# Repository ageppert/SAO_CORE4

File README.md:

# SAO_CORE4

A Nibble of Core Memory

Follow this project at: https://hackaday.io/project/197235-sao-core4-a-nibble-of-core-memory-with-i2c

Hardware Version 0.2.0 - Work in progres - reducing board size - add button - simplify.

Hardware Version 0.1.1 hand reworked prototype, simplified and re-routed row drive transistor signals to simplify firmware development. This is the version that is currently the functional prototype. These changes will be in 0.2.0.

Hardware Version 0.1 as prototyped

Hardware Version 0.1 render

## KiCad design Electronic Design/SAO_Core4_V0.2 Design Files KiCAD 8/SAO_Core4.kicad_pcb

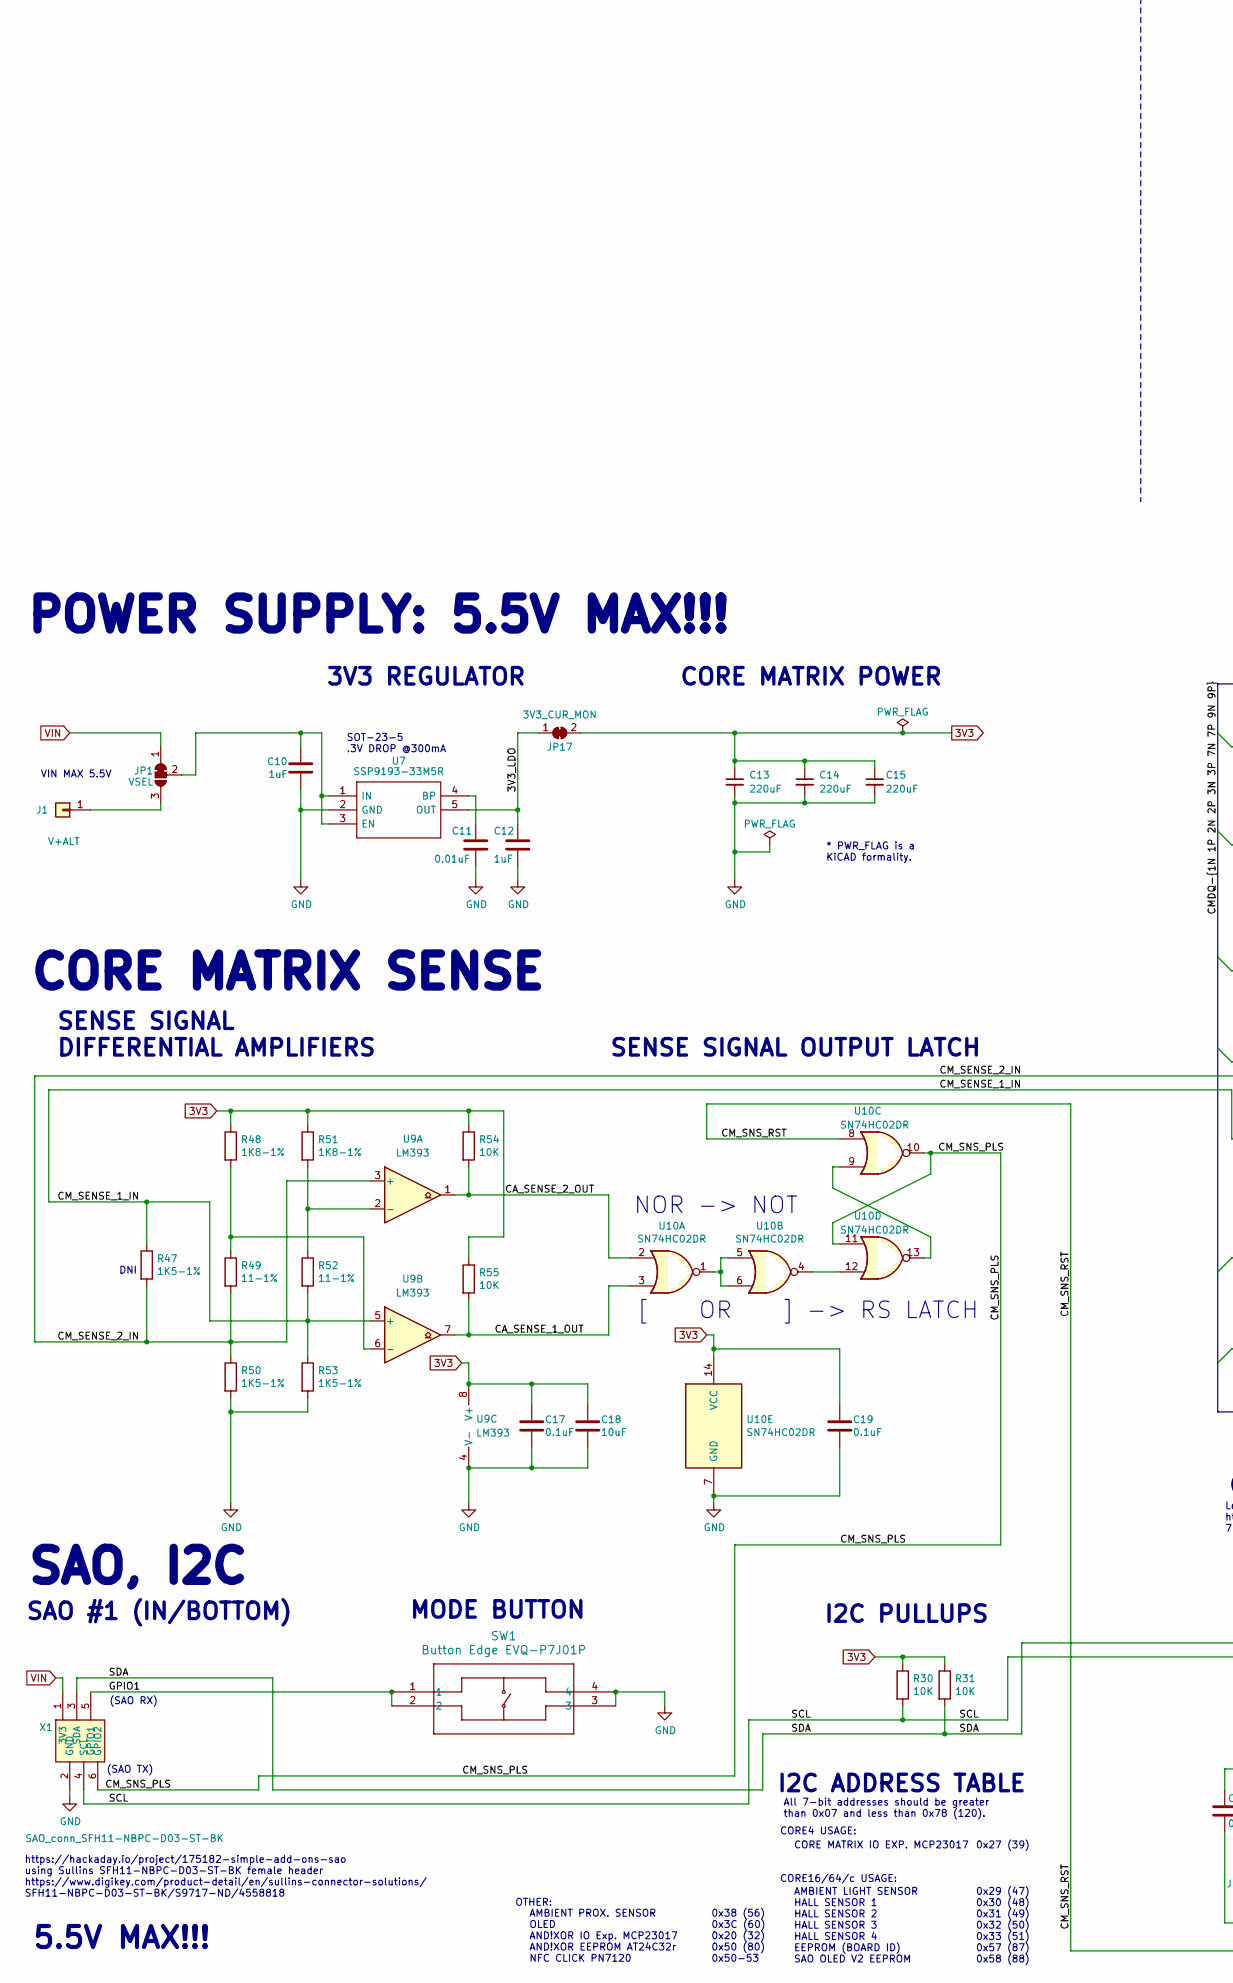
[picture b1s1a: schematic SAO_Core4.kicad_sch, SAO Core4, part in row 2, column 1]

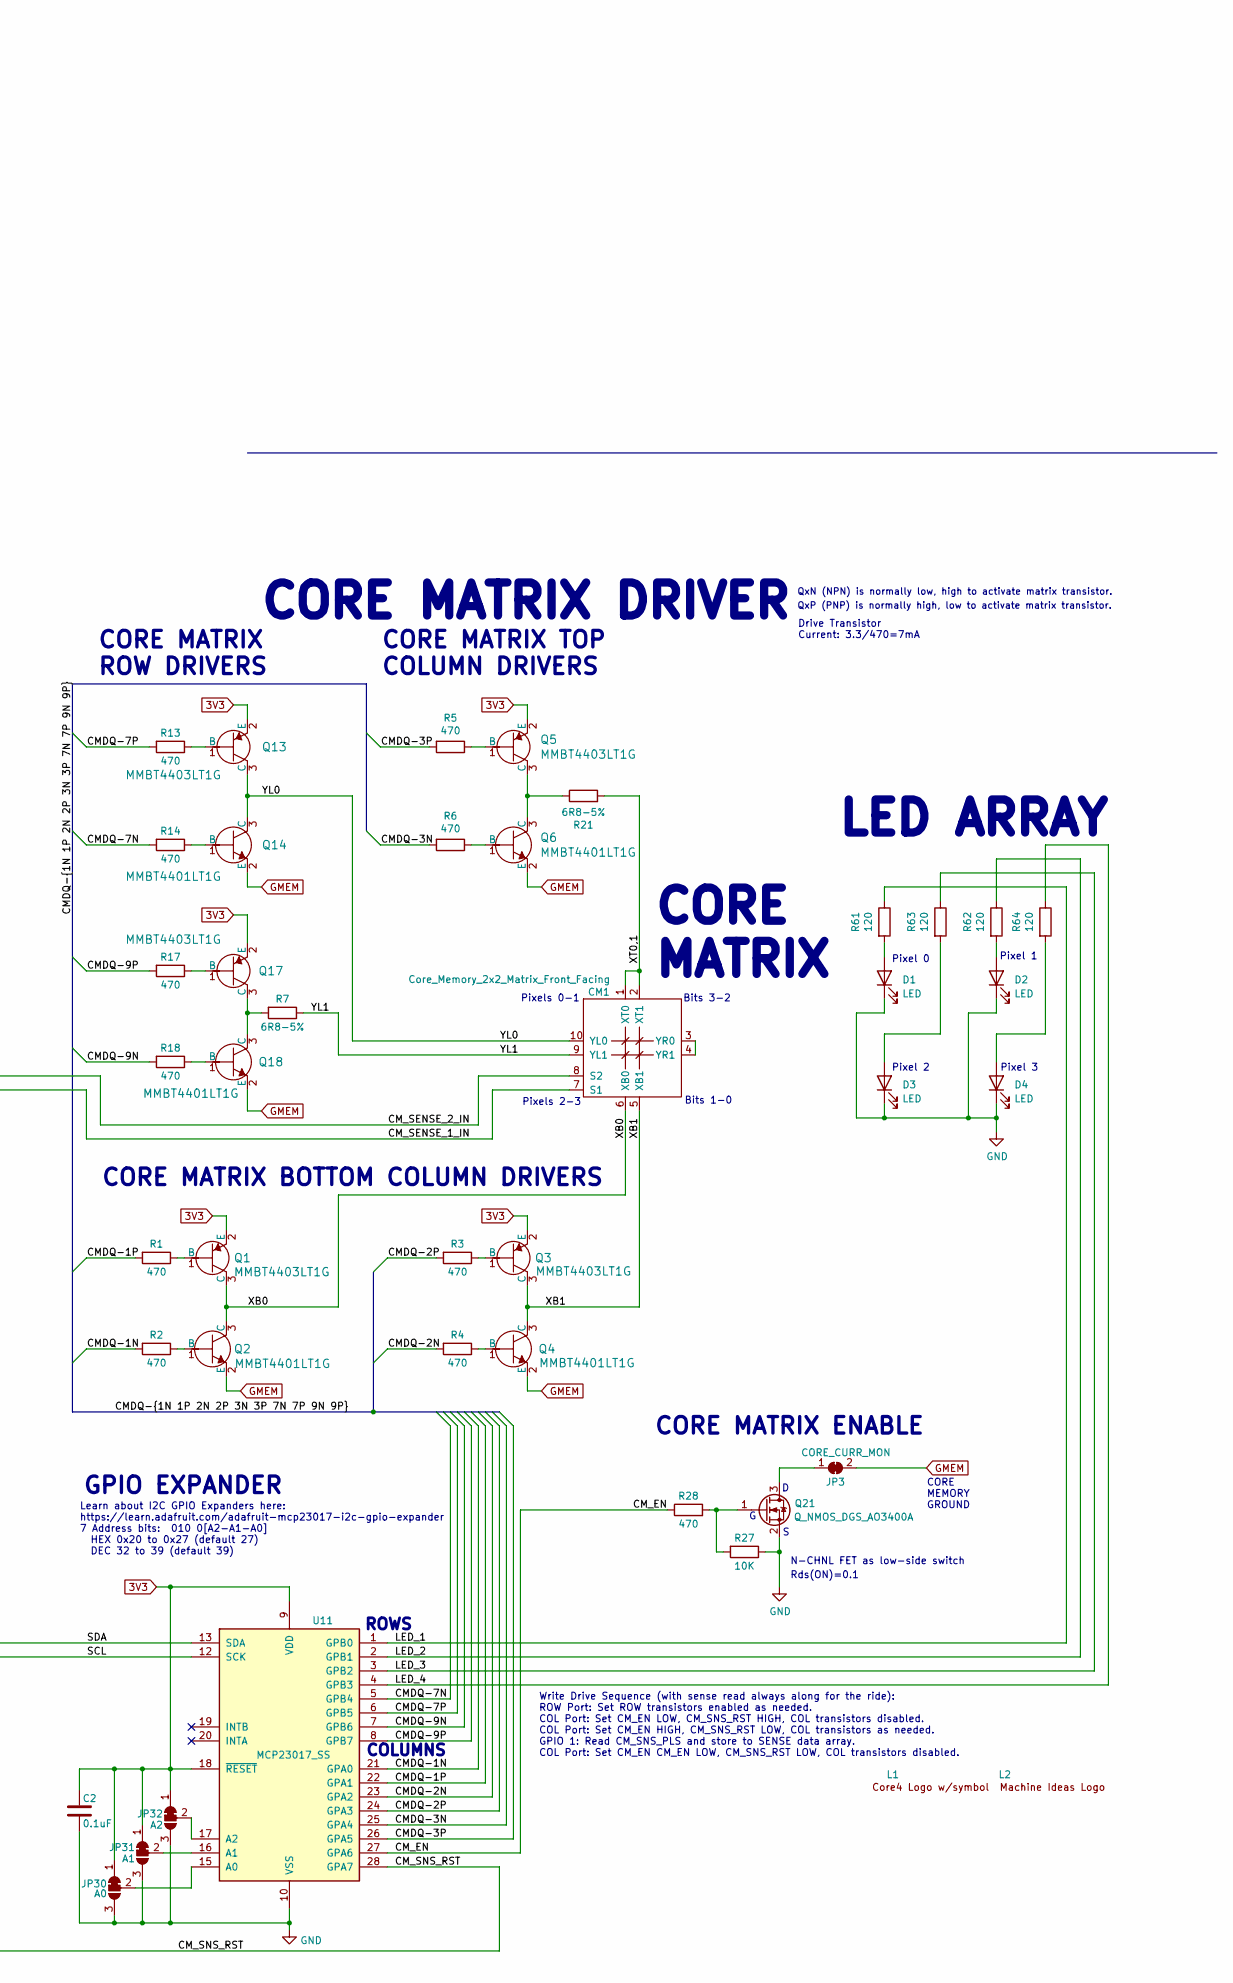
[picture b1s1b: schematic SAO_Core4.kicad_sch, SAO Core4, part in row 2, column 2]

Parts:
C2, C17, C19: 0.1uF; C_0805_2012Metric; LCSC C28233
C10, C12: 1uF; C_0805_2012Metric; LCSC C28323
C11: 0.01uF; C_0805_2012Metric; LCSC C1710
C13, C14, C15: 220uF; C_1206_3216Metric; LCSC C412252
C18: 10uF; C_0805_2012Metric; LCSC C17024
CM1: Core_Memory_2x2_Matrix_Front_Facing; core_4_6.75mm_square_front_facing
D1, D2, D3, D4: LED; LED_1206_3216Metric_RevMnt_Hole1.8x2.4mm_custom; Manufacturer_Part_Number XL-3216UOC-FB; LCSC C3646936
J1: V+ALT; PinSocket_1x01_P1.27mm_Vertical
JP1: VSEL; SolderJumper-3_P1.3mm_Bridged12_Pad1.0x1.5mm
JP3: CORE_CURR_MON; SolderJumper-2_P1.3mm_Bridged_RoundedPad1.0x1.5mm
JP17: 3V3_CUR_MON; SolderJumper-2_P1.3mm_Bridged_RoundedPad1.0x1.5mm
JP30: A0; SolderJumper-3_P1.3mm_Bridged12_Pad1.0x1.5mm
JP31: A1; SolderJumper-3_P1.3mm_Bridged12_Pad1.0x1.5mm
JP32: A2; SolderJumper-3_P1.3mm_Bridged12_Pad1.0x1.5mm
L1: Core4_w_core_symbol
L2: Machine_Ideas_logo
Q1, Q3, Q5, Q13, Q17: MMBT4403LT1G; SOT-23-3; MPN MMBT4403LT1G; Digi-Key_PN MMBT4403LT1GOSCT-ND
Q2, Q4, Q6, Q14, Q18: MMBT4401LT1G; SOT-23-3; MPN MMBT4401LT1G; Digi-Key_PN MMBT4401LT1GOSCT-ND
Q21: Q_NMOS_DGS_AO3400A; SOT-23-3; LCSC C20917
R1, R2, R3, R4, R5, R6, R13, R14, R17, R18, R28: 470; R_0805_2012Metric; LCSC C17710
R7, R21: 6R8-5%; R_0805_2012Metric; LCSC C17774
R27, R30, R31, R54, R55: 10K; R_0805_2012Metric; LCSC C17414
R47, R50, R53: 1K5-1%; R_0805_2012Metric; LCSC C4310
R48, R51: 1K8-1%; R_0805_2012Metric; LCSC C17398
R49, R52: 11-1%; R_0805_2012Metric; LCSC C17430
R61, R62, R63, R64: 120; R_0805_2012Metric; LCSC C17437
SW1: Button Edge EVQ-P7J01P; SMD4_SW_EVQP7J_PAN; LCSC C2828254
U7: SSP9193-33M5R; SOT-23-5; Manufacturer_Part_Number SGM2007-3.3XN5/TR; Mouser Part Number SGM2007-3.3XN5/TR
U9: LM393; SOIC-8_W3.9mm; LCSC C7955
U10: SN74HC02DR; SOIC-14_3.9x8.7mm_P1.27mm; MPN SN74HC02DR; LCSC C6809
U11: MCP23017_SS; SSOP-28_5.3x10.2mm_P0.65mm; LCSC C506653
X1: SAO_conn_SFH11-NBPC-D03-ST-BK; Badgelife-SAOv169-BADGE-2x3-Edge-Connect-no-front-text; MPN SFH11-NBPC-D03-ST-BK

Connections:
3V3: C2.1, C13.1, C14.1, C15.1, C17.1, C18.1, C19.1, JP17.2 (B), JP30.1 (A), JP31.1 (A), JP32.1 (A), Q1.2 (E), Q3.2 (E), Q5.2 (E), Q13.2 (E), Q17.2 (E), R30.1, R31.1, R48.1, R51.1, R54.1, R55.1, U9.8 (V+), U10.14 (VCC), U11.9 (VDD), U11.18 (~RESET)
/3V3_LDO: C12.1, JP17.1 (A), U7.5 (OUT)
/CA_SENSE_1_OUT: R55.2, U9.7, U10.3
/CA_SENSE_2_OUT: R54.2, U9.1, U10.2
/CMDQ-1N: R2.2, U11.21 (GPA0)
/CMDQ-1P: R1.2, U11.22 (GPA1)
/CMDQ-2N: R4.2, U11.23 (GPA2)
/CMDQ-2P: R3.2, U11.24 (GPA3)
/CMDQ-3N: R6.2, U11.25 (GPA4)
/CMDQ-3P: R5.2, U11.26 (GPA5)
/CMDQ-7N: R14.2, U11.5 (GPB4)
/CMDQ-7P: R13.2, U11.6 (GPB5)
/CMDQ-9N: R18.2, U11.7 (GPB6)
/CMDQ-9P: R17.2, U11.8 (GPB7)
/CM_EN: R28.1, U11.27 (GPA6)
/CM_SENSE_1_IN: CM1.7 (S1), R47.1, R52.2, R53.1, U9.5 (+)
/CM_SENSE_2_IN: CM1.8 (S2), R47.2, R49.2, R50.1, U9.3 (+)
/CM_SNS_PLS: U10.10, U10.11, X1.6 (GPIO2)
/CM_SNS_RST: U10.8, U11.28 (GPA7)
/GPIO1: SW1.1, SW1.2, X1.5 (GPIO1)
/LED_1: R61.1, U11.1 (GPB0)
/LED_2: R62.1, U11.2 (GPB1)
/LED_3: R63.1, U11.3 (GPB2)
/LED_4: R64.1, U11.4 (GPB3)
/SCL: R30.2, U11.12 (SCK), X1.4 (SCL)
/SDA: R31.2, U11.13 (SDA), X1.3 (SDA)
/XB0: CM1.6 (XB0), Q1.3 (C), Q2.3 (C)
/XB1: CM1.5 (XB1), Q3.3 (C), Q4.3 (C)
/XT0,1: CM1.1 (XT0), CM1.2 (XT1), R21.2
/YL0: CM1.10 (YL0), Q13.3 (C), Q14.3 (C)
/YL1: CM1.9 (YL1), R7.1
GMEM: JP3.2 (B), Q2.2 (E), Q4.2 (E), Q6.2 (E), Q14.2 (E), Q18.2 (E)
GND: C2.2, C10.2, C11.2, C12.2, C13.2, C14.2, C15.2, C17.2, C18.2, C19.2, D1.1 (K), D2.1 (K), D3.1 (K), D4.1 (K), JP30.3 (B), JP31.3 (B), JP32.3 (B), Q21.2 (S), R27.1, R50.2, R53.2, SW1.3, SW1.4, U7.2 (GND), U9.4 (V-), U10.7 (GND), U11.10 (VSS), X1.2 (GND)
unnamed: CM1.3 (YR0), CM1.4 (YR1)
unnamed: D1.2 (A), R61.2
unnamed: D2.2 (A), R62.2
unnamed: D3.2 (A), R63.2
unnamed: D4.2 (A), R64.2
unnamed: J1.1, JP1.3 (B)
unnamed: C10.1, JP1.2 (C), U7.1 (IN), U7.3 (EN)
unnamed: JP3.1 (A), Q21.3 (D)
unnamed: JP30.2 (C), U11.15 (A0)
unnamed: JP31.2 (C), U11.16 (A1)
unnamed: JP32.2 (C), U11.17 (A2)
unnamed: Q1.1 (B), R1.1
unnamed: Q2.1 (B), R2.1
unnamed: Q3.1 (B), R3.1
unnamed: Q4.1 (B), R4.1
unnamed: Q5.1 (B), R5.1
unnamed: Q5.3 (C), Q6.3 (C), R21.1
unnamed: Q6.1 (B), R6.1
unnamed: Q13.1 (B), R13.1
unnamed: Q14.1 (B), R14.1
unnamed: Q17.1 (B), R17.1
unnamed: Q17.3 (C), Q18.3 (C), R7.2
unnamed: Q18.1 (B), R18.1
unnamed: Q21.1 (G), R27.2, R28.2
unnamed: C11.1, U7.4 (BP)
unnamed: R51.2, R52.1, U9.2 (-)
unnamed: R48.2, R49.1, U9.6 (-)
unnamed: U10.1, U10.5, U10.6
unnamed: U10.4, U10.12
unnamed: U10.9, U10.13
VIN: JP1.1 (A), X1.1 (3V3)

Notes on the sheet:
Bits 1-0
Pixel 0
QxP (PNP) is normally high, low to activate matrix transistor.
NOR -> NOT
AMBIENT PROX. SENSOR OLED AND!XOR IO Exp. MCP23017 AND!XOR EEPROM AT24C32r NFC CLICK PN7120
https://hackaday.io/project/175182-simple-add-ons-sao using Sullins SFH11-NBPC-D03-ST-BK female header https://www.digikey.com/product-detail/en/sullins-connector-solutions/ SFH11-NBPC-D03-ST-BK/S9717-ND/4558818
Bits 3-2
CORE MEMORY GROUND
N-CHNL FET as low-side switch
SENSE SIGNAL OUTPUT LATCH
[ OR ] -> RS LATCH
CORE MATRIX ROW DRIVERS
CORE4 USAGE:
CORE MATRIX IO EXP. MCP23017
Pixels 0-1
CORE MATRIX BOTTOM COLUMN DRIVERS
SOT-23-5 .3V DROP @300mA
MODE BUTTON
0x29 (47) 0x30 (48) 0x31 (49) 0x32 (50) 0x33 (51) 0x57 (87) 0x58 (88)
QxN (NPN) is normally low, high to activate matrix transistor.
ROWS
Pixel 2
COLUMNS
* PWR_FLAG is a KiCAD formality.
Pixel 1
GPIO EXPANDER
Rds(ON)=0.1
AMBIENT LIGHT SENSOR HALL SENSOR 1 HALL SENSOR 2 HALL SENSOR 3 HALL SENSOR 4 EEPROM (BOARD ID) SAO OLED V2 EEPROM
CORE MATRIX ENABLE
POWER SUPPLY: 5.5V MAX!!!
Drive Transistor Current: 3.3/470=7mA
CORE MATRIX DRIVER
CORE MATRIX TOP COLUMN DRIVERS
5.5V MAX!!!
3V3 REGULATOR
VIN MAX 5.5V
(SAO TX)
Write Drive Sequence (with sense read always along for the ride): ROW Port: Set ROW transistors enabled as needed. COL Port: Set CM_EN LOW, CM_SNS_RST HIGH, COL transistors disabled. COL Port: Set CM_EN HIGH, CM_SNS_RST LOW, COL transistors as needed. GPIO 1: Read CM_SNS_PLS and store to SENSE data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
0x38 (56) 0x3C (60) 0x20 (32) 0x50 (80) 0x50-53
SAO #1 (IN/BOTTOM)

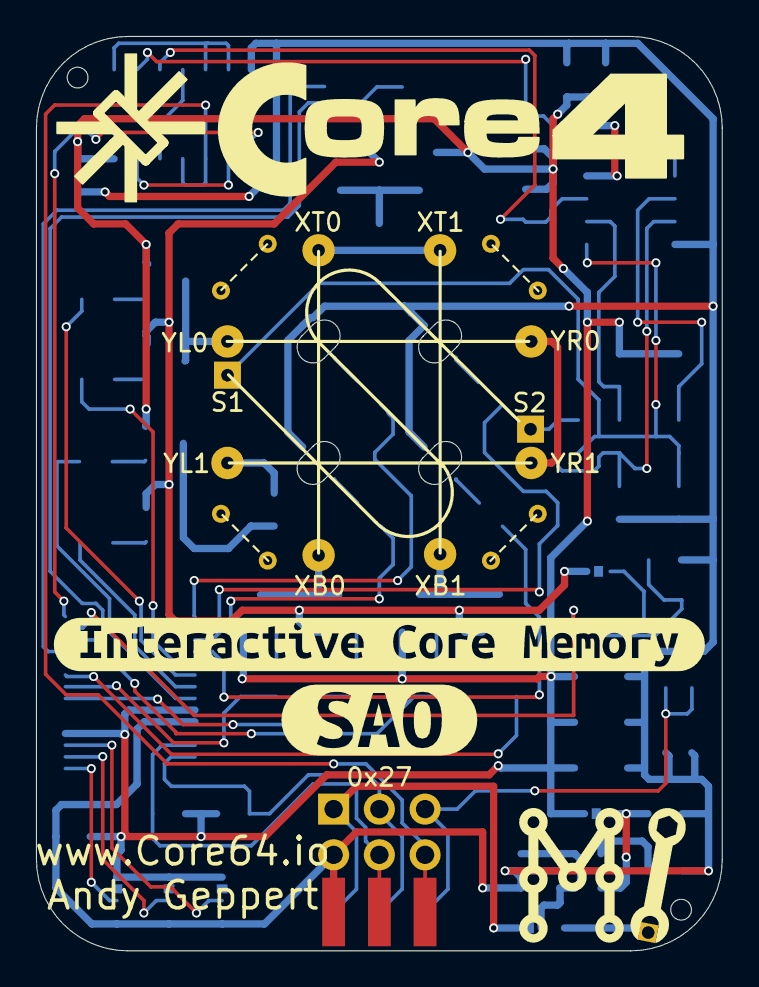
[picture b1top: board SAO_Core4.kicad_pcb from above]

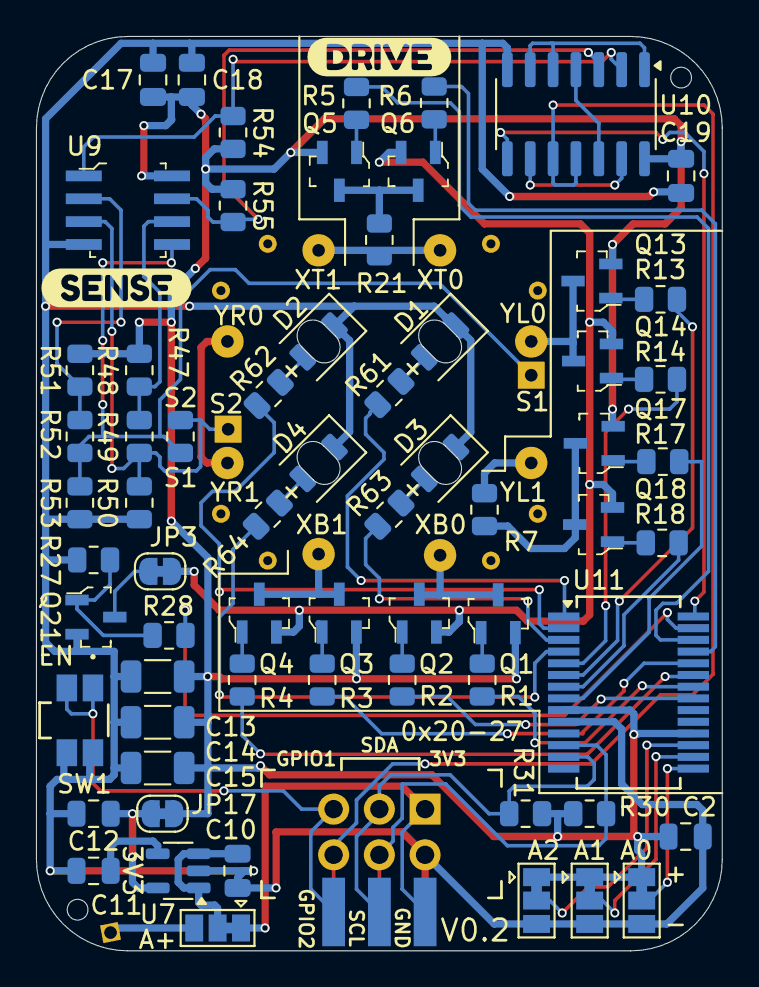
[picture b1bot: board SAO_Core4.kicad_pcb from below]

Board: 2 copper layers, 38.1 x 50.8 mm, 74 parts (68 on the bottom side), 64 nets.

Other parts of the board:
kibuzzard-66D35F07: G***; kibuzzard-66D35F07
kibuzzard-66D35F61: G***; kibuzzard-66D35F61
kibuzzard-64178DE8: G***; kibuzzard-64178DE8
kibuzzard-64178DF4: G***; kibuzzard-64178DF4

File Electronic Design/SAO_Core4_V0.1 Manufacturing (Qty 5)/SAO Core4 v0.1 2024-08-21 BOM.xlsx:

Comment | Designator | Footprint | LCSC Part Number | Substituted
0.1uF | C2, C17, C19 | Capacitor_SMD:C_0805_2012Metric | C28233
1uF | C10, C12 | Capacitor_SMD:C_0805_2012Metric | C28323
0.01uF | C11 | Capacitor_SMD:C_0805_2012Metric | C1710
220uF | C13, C14, C15 | Capacitor_SMD:C_1206_3216Metric | C412252
10uF | C18 | Capacitor_SMD:C_0805_2012Metric | C17024
LED | D1, D2, D3, D4 | Andy_Footprint_Library:LED_1206_3216Metric_RevMnt_Hole1.8x2.4mm_custom | C3646936
MMBT4403LT1G | Q1, Q3, Q5, Q13, Q17 | digikey-footprints:SOT-23-3 | C78864
MMBT4401LT1G | Q2, Q4, Q6, Q14, Q18 | digikey-footprints:SOT-23-3 | C31776
Q_NMOS_DGS_AO3400A | Q21 | digikey-footprints:SOT-23-3 | C20917
SL3401A | Q22 | digikey-footprints:SOT-23-3 | C350311
470 | R1, R2, R3, R4, R5, R6, R13, R14, R17, R18, R28 | Resistor_SMD:R_0805_2012Metric | C17710
8R2-5% | R7, R21 | Resistor_SMD:R_0805_2012Metric | C17830
4K7 | R27, R44 | Resistor_SMD:R_0805_2012Metric | C17673
1K2 | R30, R31, R54, R55 | Resistor_SMD:R_0805_2012Metric | C17379
0 | R32, R33 | Resistor_SMD:R_0805_2012Metric | C17477
1K5-1% | R47, R50, R53 | Resistor_SMD:R_0805_2012Metric | C4310
1K8-1% | R48, R51 | Resistor_SMD:R_0805_2012Metric | C17398
11-1% | R49, R52 | Resistor_SMD:R_0805_2012Metric | C17430
120 | R60, R61, R62, R63 | Resistor_SMD:R_0805_2012Metric | C17437
SSP9193-33M5R | U7 | Package_TO_SOT_SMD:SOT-23-5 | C411022
LM393 | U9 | Andy_Footprint_Library:SOIC-8_W3.9mm | C7955
SN74HC02DR | U10 | Package_SO:SOIC-14_3.9x8.7mm_P1.27mm | C350559
MCP23017_SS | U11 | Package_SO:SSOP-28_5.3x10.2mm_P0.65mm | C506653
QWIIC | X9 | Connector_JST:JST_SH_SM04B-SRSS-TB_1x04-1MP_P1.00mm_Horizontal | C160404

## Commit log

2024-08-14 First draft in progress
2024-08-14 Update README.md
    Add Hackaday Project Link
2024-08-17 Refine
    Cleanup schematic, plan drive scheme, commit to CM_EN, spare IO.
2024-08-18 Refine schematic
2024-08-18 .DS_Store banished!
2024-08-18 .gitattributes banished!
2024-08-23 HWV0.1 as prototyped
    Design as released, files organized.
2024-08-23 Copy HWV0.1 to start HWV0.2 design files
2024-08-23 Clean-up readme, add [correct] image
2024-08-23 Clean-up schematic DRC
2024-08-31 Begin refinements for HWV0.2.0
2024-08-31 Begin demo code in Arduino with dazzling LEDs
2024-09-01 Send single byte to each MCP register
2024-09-01 HWV0.2.0: Move silkscreen elements
2024-09-01 Flux detect works in all cores with Arduino demo code
2024-09-01 Demo code clean-up
2024-09-01 Shrink V0.2 PCB size
2024-09-03 Working game of memory!
2024-09-03 Move LED dazzle to occur with memory game randomizer in Arduino demo
2024-09-03 Add V0.1 to schematics and renders
2024-09-03 HWV0.2: Create WIP schematics pdf and renders
2024-09-03 Add license, update readme pics
2024-09-03 Fix image links in readme
2024-09-03 Reduce V0.2 render image height to show size difference
2024-09-10 Create assembly guide.
2024-09-10 Add schematic revision 0.1.1 redlines to Assembly Guide
2024-09-10 Add schematic revision V0.1.1 redlines
2024-09-10 HWV0.2: Denote as WIP
2024-09-10 Update HWV0.1.1 image with revision change sticker
2024-09-21 Add delay after all core writes to reduce average current use
2024-10-10 Add SAo Core4 V0.2 files, demo code update
2026-05-18 Add screen protector template
2026-05-18 File cleanup
2026-05-29 Fix Firmware Demo CoreMemoryBitWrite, default to HWV 0.2.0, default to NeoPixel enable
    Fully operational! Backed out changes that broke the operation of Game of Memory operation.
